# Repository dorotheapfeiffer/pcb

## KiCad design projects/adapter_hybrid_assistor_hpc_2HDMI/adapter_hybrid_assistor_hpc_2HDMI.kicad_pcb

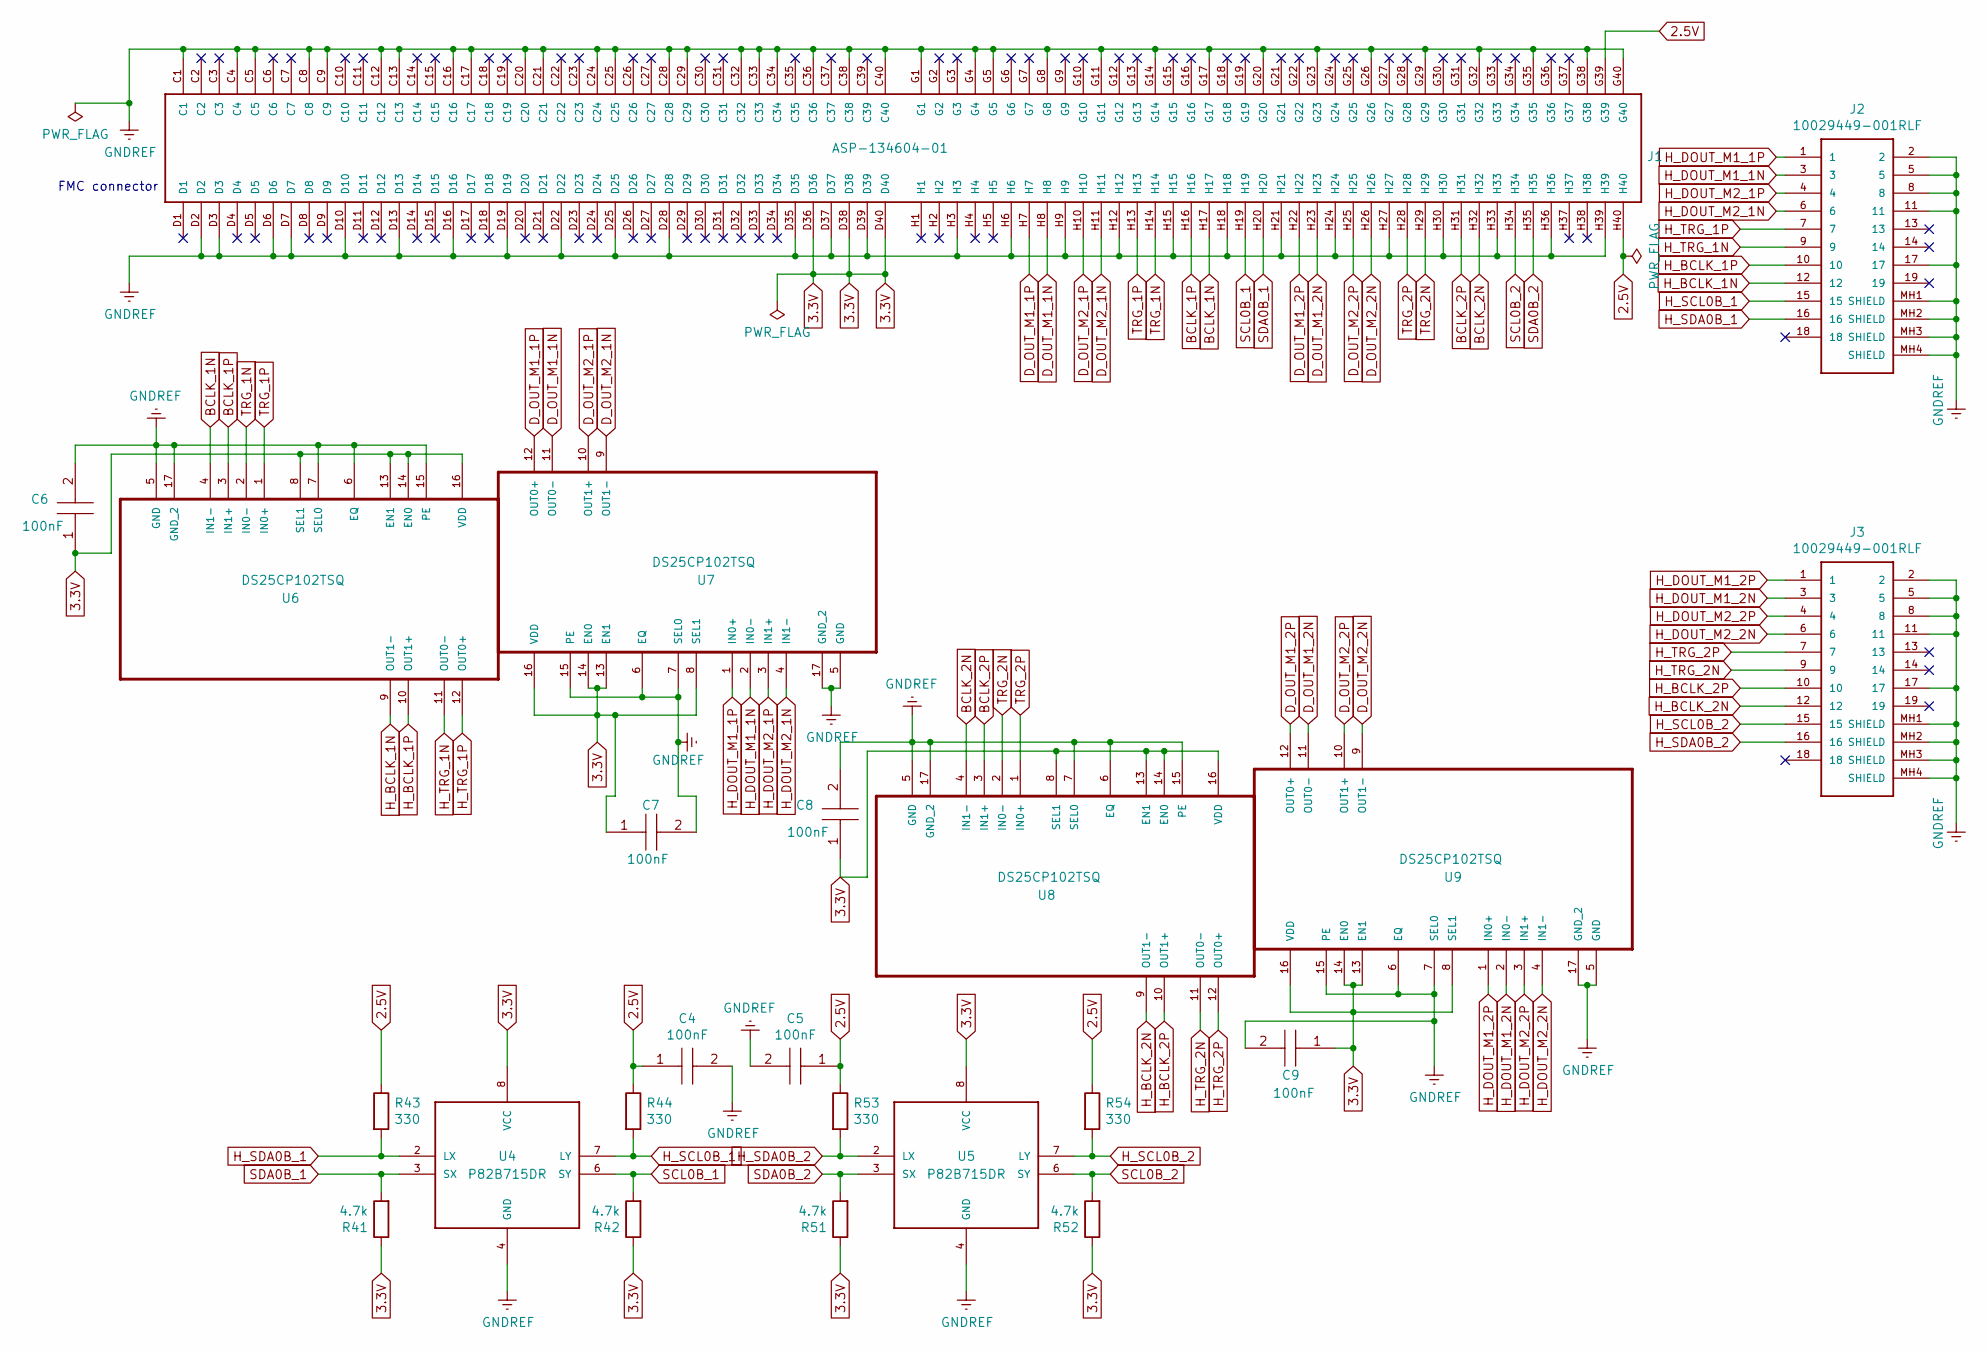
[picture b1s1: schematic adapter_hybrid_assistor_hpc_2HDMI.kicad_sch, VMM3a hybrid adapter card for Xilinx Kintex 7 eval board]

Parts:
C4, C5, C6, C7, C8, C9: 100nF; C0603C104K4RACTU; Manufacturer_Part_Number C0603C104K4RACTU; Mouser Part Number 80-C0603C104K4R
J1: ASP-134604-01; Samtec_FMC_ASP-134604-01_4x40_Vertical
J2, J3: 10029449-001RLF; 10029449001RLF
R41, R42, R51, R52: 4.7k; R_0603_1608Metric
R43, R44, R53, R54: 330; R_0603_1608Metric
U4, U5: P82B715DR
U6, U7, U8, U9: DS25CP102TSQ; QFN50P400X400X80-17N

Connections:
2.5V: C4.1, C5.1, J1.G39, J1.H40, R43.1, R44.1, R53.1, R54.1
3.3V: C6.1, C7.1, C8.1, C9.1, J1.D36, J1.D38, J1.D40, R41.1, R42.1, R51.1, R52.1, U4.8 (VCC), U5.8 (VCC), U6.8 (SEL1), U6.13 (EN1), U6.14 (EN0), U6.16 (VDD), U7.8 (SEL1), U7.13 (EN1), U7.14 (EN0), U7.16 (VDD), U8.8 (SEL1), U8.13 (EN1), U8.14 (EN0), U8.16 (VDD), U9.8 (SEL1), U9.13 (EN1), U9.14 (EN0), U9.16 (VDD)
BCLK_1N: J1.H17, U6.4 (IN1-)
BCLK_1P: J1.H16, U6.3 (IN1+)
BCLK_2N: J1.H32, U8.4 (IN1-)
BCLK_2P: J1.H31, U8.3 (IN1+)
D_OUT_M1_1N: J1.H8, U7.11 (OUT0-)
D_OUT_M1_1P: J1.H7, U7.12 (OUT0+)
D_OUT_M1_2N: J1.H23, U9.11 (OUT0-)
D_OUT_M1_2P: J1.H22, U9.12 (OUT0+)
D_OUT_M2_1N: J1.H11, U7.9 (OUT1-)
D_OUT_M2_1P: J1.H10, U7.10 (OUT1+)
D_OUT_M2_2N: J1.H26, U9.9 (OUT1-)
D_OUT_M2_2P: J1.H25, U9.10 (OUT1+)
GNDREF: C4.2, C5.2, C6.2, C7.2, C8.2, C9.2, J1.C1, J1.C4, J1.C5, J1.C8, J1.C9, J1.C12, J1.C13, J1.C16, J1.C17, J1.C20, J1.C21, J1.C24, J1.C25, J1.C28, J1.C29, J1.C32, J1.C33, J1.C34, J1.C36, J1.C38, J1.C40, J1.D2, J1.D3, J1.D6, J1.D7, J1.D10, J1.D13, J1.D16, J1.D19, J1.D22, J1.D25, J1.D28, J1.D35, J1.D37, J1.D39, J1.G1, J1.G4, J1.G5, J1.G8, J1.G11, J1.G14, J1.G17, J1.G20, J1.G23, J1.G26, J1.G29, J1.G32, J1.G35, J1.G38, J1.G40, J1.H3, J1.H6, J1.H9, J1.H12, J1.H15, J1.H18, J1.H21, J1.H24, J1.H27, J1.H30, J1.H33, J1.H36, J1.H39, J2.2, J2.5, J2.8, J2.11, J2.17, J2.MH1 (SHIELD), J2.MH2 (SHIELD), J2.MH3 (SHIELD), J2.MH4 (SHIELD), J3.2, J3.5, J3.8, J3.11, J3.17, J3.MH1 (SHIELD), J3.MH2 (SHIELD), J3.MH3 (SHIELD), J3.MH4 (SHIELD), U4.4 (GND), U5.4 (GND), U6.5 (GND), U6.6 (EQ), U6.7 (SEL0), U6.15 (PE), U6.17 (GND_2), U7.5 (GND), U7.6 (EQ), U7.7 (SEL0), U7.15 (PE), U7.17 (GND_2), U8.5 (GND), U8.6 (EQ), U8.7 (SEL0), U8.15 (PE), U8.17 (GND_2), U9.5 (GND), U9.6 (EQ), U9.7 (SEL0), U9.15 (PE), U9.17 (GND_2)
H_BCLK_1N: J2.12, U6.9 (OUT1-)
H_BCLK_1P: J2.10, U6.10 (OUT1+)
H_BCLK_2N: J3.12, U8.9 (OUT1-)
H_BCLK_2P: J3.10, U8.10 (OUT1+)
H_DOUT_M1_1N: J2.3, U7.2 (IN0-)
H_DOUT_M1_1P: J2.1, U7.1 (IN0+)
H_DOUT_M1_2N: J3.3, U9.2 (IN0-)
H_DOUT_M1_2P: J3.1, U9.1 (IN0+)
H_DOUT_M2_1N: J2.6, U7.4 (IN1-)
H_DOUT_M2_1P: J2.4, U7.3 (IN1+)
H_DOUT_M2_2N: J3.6, U9.4 (IN1-)
H_DOUT_M2_2P: J3.4, U9.3 (IN1+)
H_SCL0B_1: J2.15, R44.2, U4.7 (LY)
H_SCL0B_2: J3.15, R54.2, U5.7 (LY)
H_SDA0B_1: J2.16, R43.2, U4.2 (LX)
H_SDA0B_2: J3.16, R53.2, U5.2 (LX)
H_TRG_1N: J2.9, U6.11 (OUT0-)
H_TRG_1P: J2.7, U6.12 (OUT0+)
H_TRG_2N: J3.9, U8.11 (OUT0-)
H_TRG_2P: J3.7, U8.12 (OUT0+)
SCL0B_1: J1.H19, R42.2, U4.6 (SY)
SCL0B_2: J1.H34, R52.2, U5.6 (SY)
SDA0B_1: J1.H20, R41.2, U4.3 (SX)
SDA0B_2: J1.H35, R51.2, U5.3 (SX)
TRG_1N: J1.H14, U6.2 (IN0-)
TRG_1P: J1.H13, U6.1 (IN0+)
TRG_2N: J1.H29, U8.2 (IN0-)
TRG_2P: J1.H28, U8.1 (IN0+)

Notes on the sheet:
FMC connector

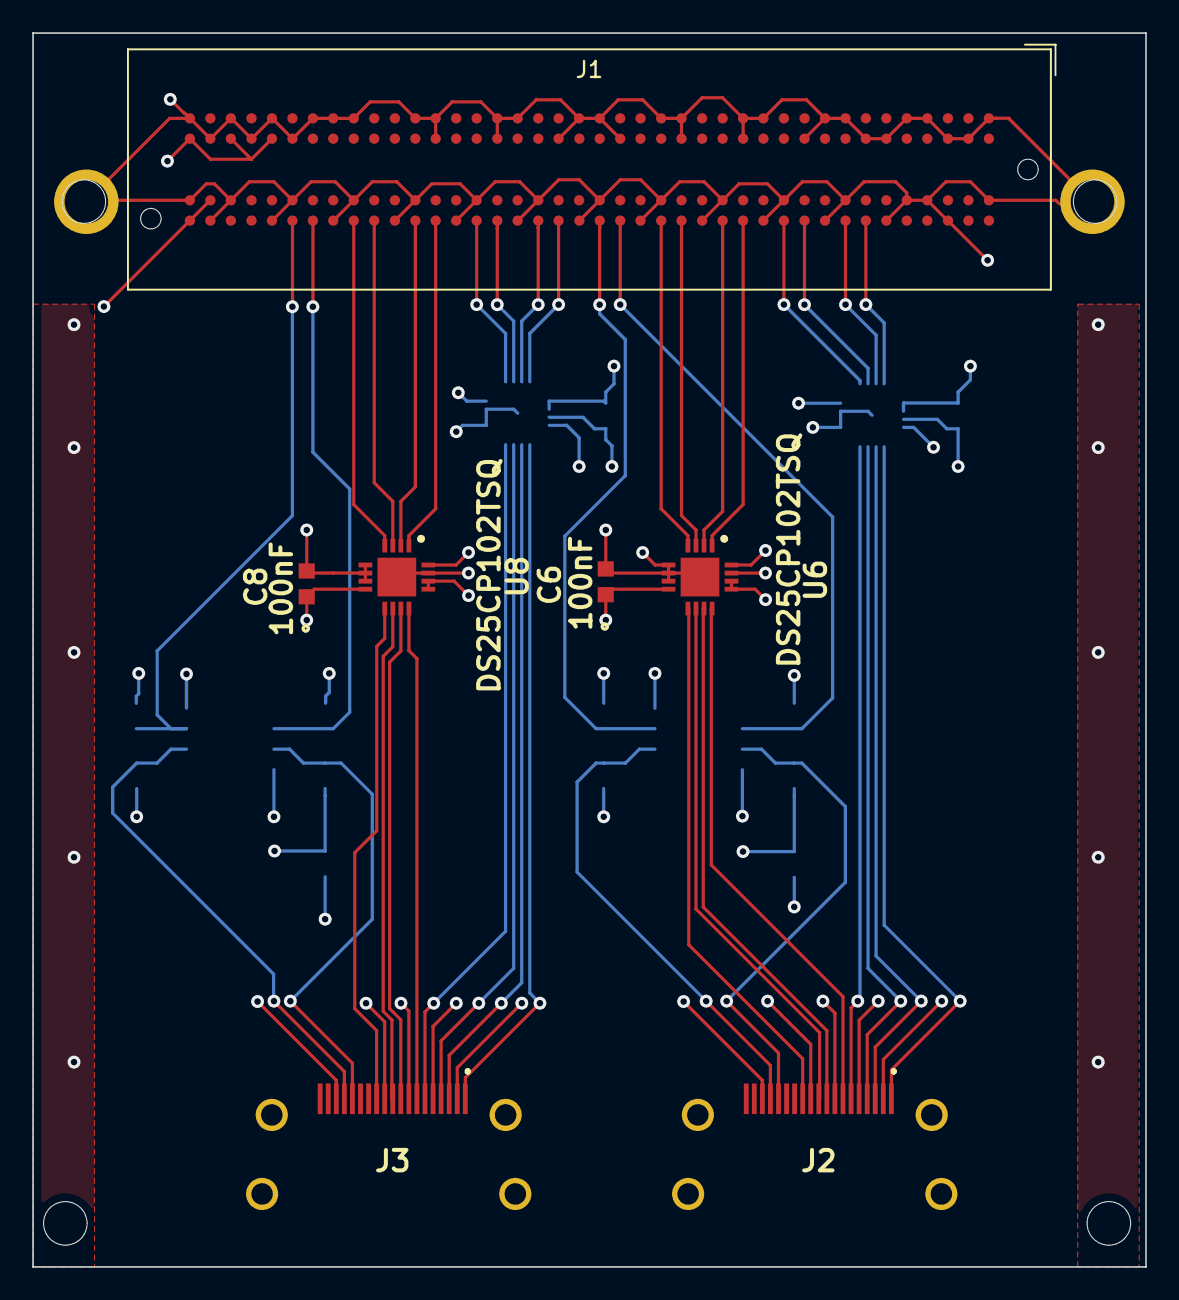
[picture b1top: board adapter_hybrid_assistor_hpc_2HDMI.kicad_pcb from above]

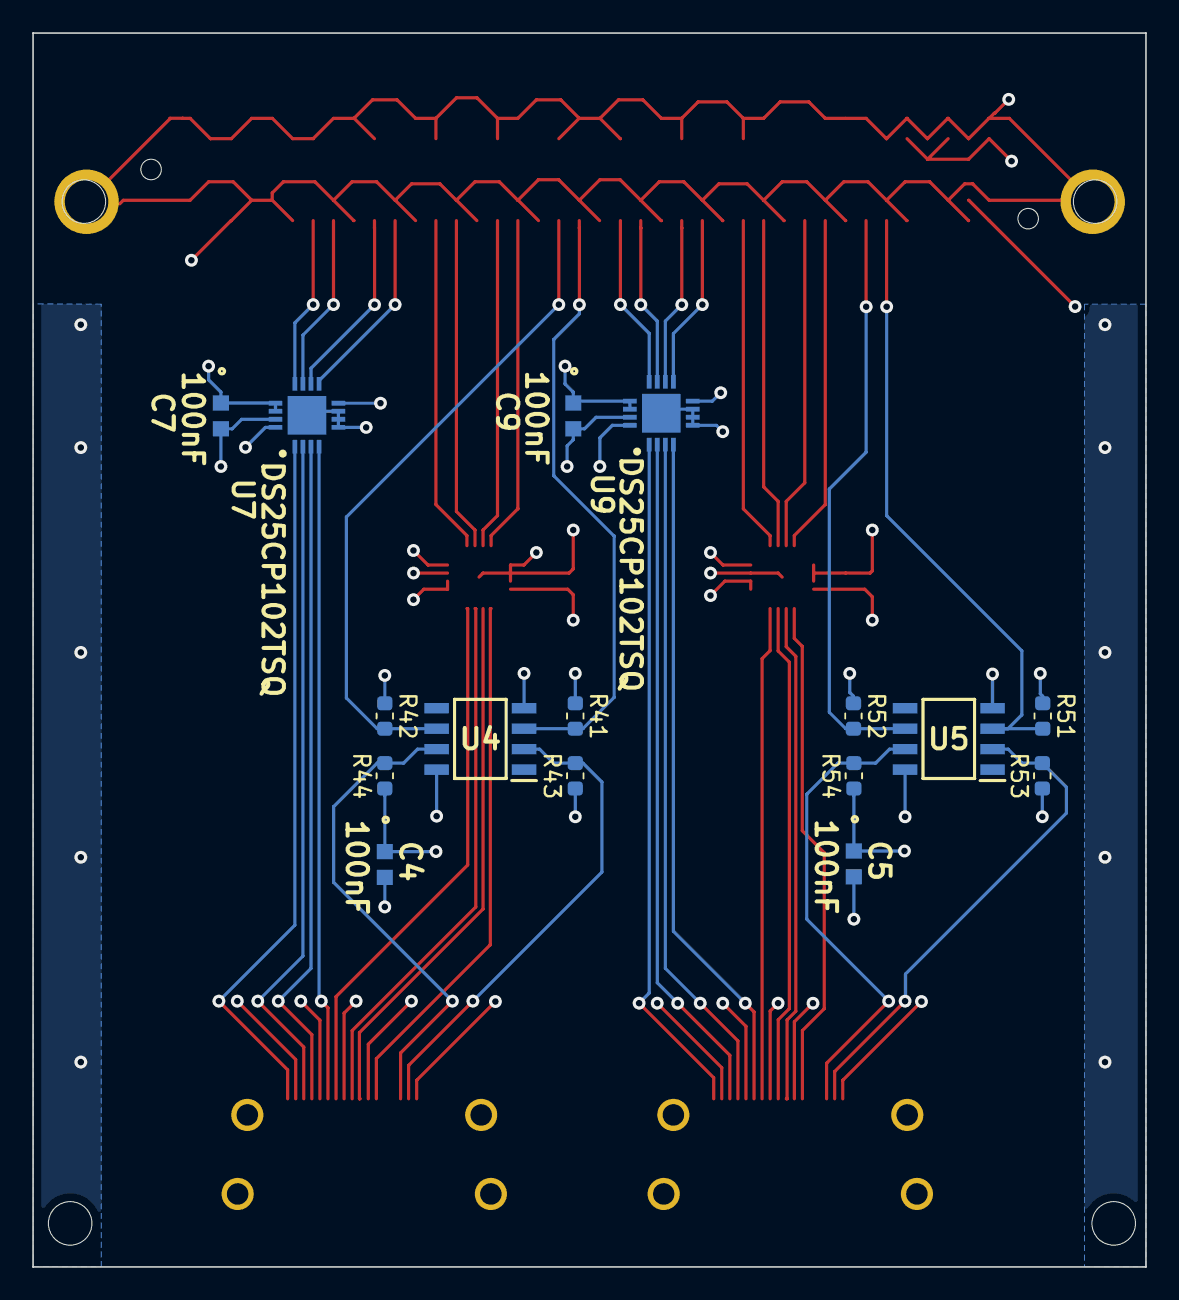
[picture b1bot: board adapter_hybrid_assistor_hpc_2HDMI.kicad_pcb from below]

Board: 4 copper layers, 69.0 x 76.5 mm, 23 parts (16 on the bottom side), 43 nets.

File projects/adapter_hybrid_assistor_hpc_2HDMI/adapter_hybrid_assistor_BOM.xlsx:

Id | Designator | Designation | Package | Quantity | Value | Place_YES/NO | Provided_by_customer_YES/NO | Supplier | Supplier ref | Manufacturer | Montage
2 | J1 | ASP13460401 |  | 1 |  | YES | NO | Mouser | 200-ASP-134604-01 | Samtec | Solder Balls
6 | U7,U6,U9,U8 | DS25CP102TSQ | WQFN-16 | 4 |  | YES | NO | Mouser | 926-DS25CP102TSQNOPB | Texas Instruments | SMD/SMT
7 | U5,U4 | P82B715DR | SOIC-8 | 2 |  | YES | NO | Mouser | 595-P82B715DR | Texas Instruments | SMD/SMT
11 | J2,J3 | 10029449001RLF |  | 2 |  | YES | NO | Mouser | 649-10029449-001RLF | Amphenol FCI | SMD/SMT
12 | R41,R42,R51,R52 | ERA-3ARB472V | 0603 (1608 metric) | 4 | 4.7k | YES | NO | Mouser | ERA3ARB472V | Panasonic | SMD/SMT | ERA3ARB472V
14 | R43,R44,R53,R54 | ERA-3AED331V | 0603 (1608 metric) | 4 | 330 | YES | NO | Mouser | ERA3AEB331V | Panasonic | SMD/SMT | ERA3AEB331V
15 | C4,C5,C6,C7,C8,C9 | C0603C104K4RACTU | 0603 (1608 metric) | 6 | 100nF | YES | NO | Mouser | 80-C0603C104K4R | KEMET | SMD/SMT
 |  |  |  | 23

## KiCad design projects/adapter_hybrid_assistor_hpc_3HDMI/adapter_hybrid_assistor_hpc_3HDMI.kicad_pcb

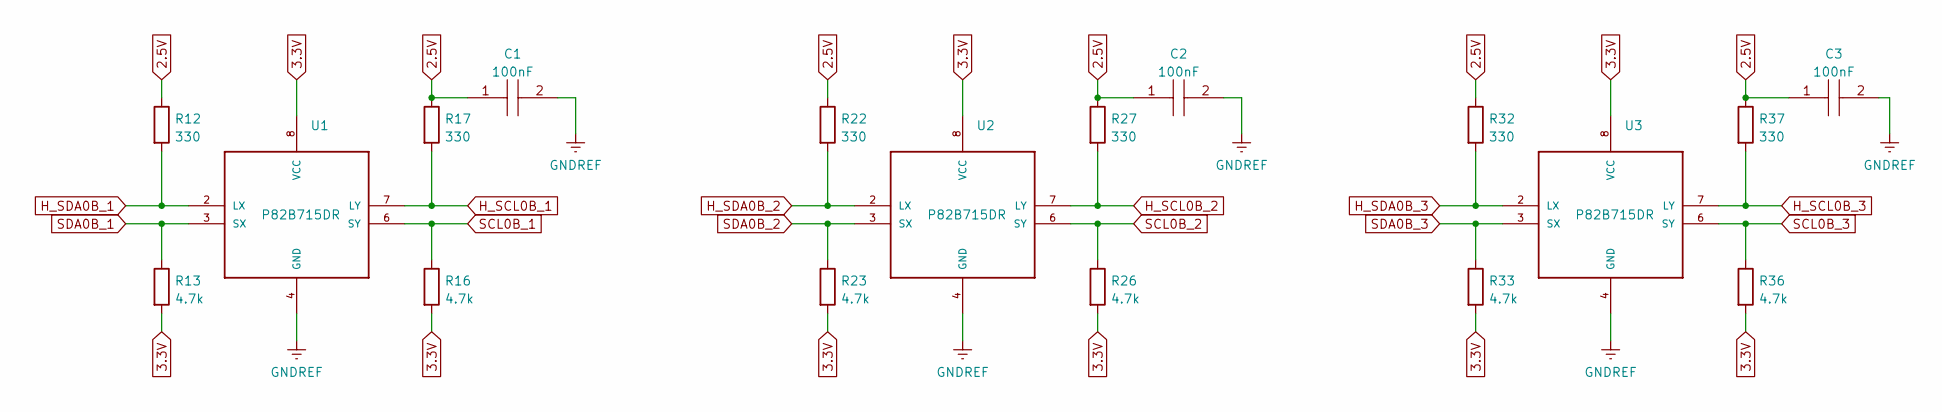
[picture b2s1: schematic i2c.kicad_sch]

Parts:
C1, C2, C3: 100nF; C0603C104K4RACTU; Manufacturer_Part_Number C0603C104K4RACTU; Mouser Part Number 80-C0603C104K4R
R12, R17, R22, R27, R32, R37: 330; R_0603_1608Metric
R13, R16, R23, R26, R33, R36: 4.7k; R_0603_1608Metric
U1, U2, U3: P82B715DR

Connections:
2.5V: C1.1, C2.1, C3.1, R12.1, R17.1, R22.1, R27.1, R32.1, R37.1; also elsewhere on the board
3.3V: R13.2, R16.2, R23.2, R26.2, R33.2, R36.2, U1.8 (VCC), U2.8 (VCC), U3.8 (VCC); also elsewhere on the board
H_SCL0B_1: R17.2, U1.7 (LY); also elsewhere on the board
H_SCL0B_2: R27.2, U2.7 (LY); also elsewhere on the board
H_SCL0B_3: R37.2, U3.7 (LY); also elsewhere on the board
H_SDA0B_1: R12.2, U1.2 (LX); also elsewhere on the board
H_SDA0B_2: R22.2, U2.2 (LX); also elsewhere on the board
H_SDA0B_3: R32.2, U3.2 (LX); also elsewhere on the board
SCL0B_1: R16.1, U1.6 (SY); also elsewhere on the board
SCL0B_2: R26.1, U2.6 (SY); also elsewhere on the board
SCL0B_3: R36.1, U3.6 (SY); also elsewhere on the board
SDA0B_1: R13.1, U1.3 (SX); also elsewhere on the board
SDA0B_2: R23.1, U2.3 (SX); also elsewhere on the board
SDA0B_3: R33.1, U3.3 (SX); also elsewhere on the board

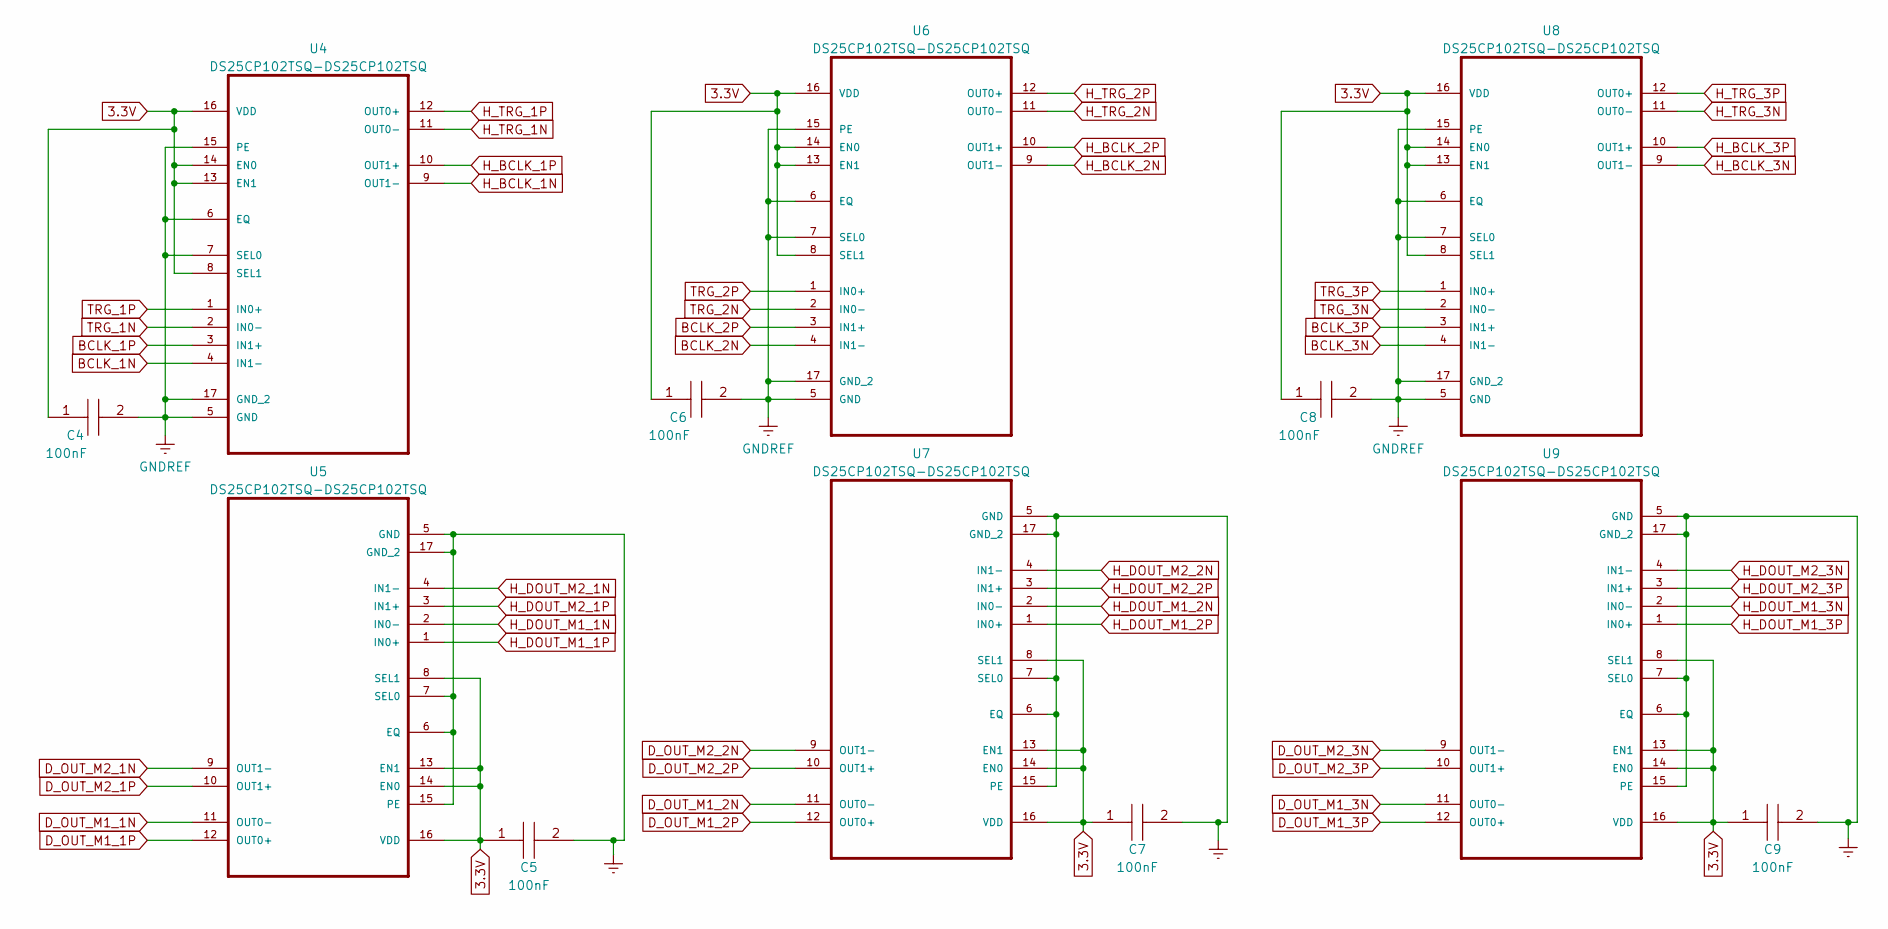
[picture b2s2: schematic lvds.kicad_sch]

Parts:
C4, C5, C6, C7, C8, C9: 100nF; C0603C104K4RACTU; Manufacturer_Part_Number C0603C104K4RACTU; Mouser Part Number 80-C0603C104K4R
U4, U5, U6, U7, U8, U9: DS25CP102TSQ-DS25CP102TSQ; QFN50P400X400X80-17N

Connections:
3.3V: C4.1, C5.1, C6.1, C7.1, C8.1, C9.1, U4.8 (SEL1), U4.13 (EN1), U4.14 (EN0), U4.16 (VDD), U5.8 (SEL1), U5.13 (EN1), U5.14 (EN0), U5.16 (VDD), U6.8 (SEL1), U6.13 (EN1), U6.14 (EN0), U6.16 (VDD), U7.8 (SEL1), U7.13 (EN1), U7.14 (EN0), U7.16 (VDD), U8.8 (SEL1), U8.13 (EN1), U8.14 (EN0), U8.16 (VDD), U9.8 (SEL1), U9.13 (EN1), U9.14 (EN0), U9.16 (VDD); also elsewhere on the board
BCLK_1N: U4.4 (IN1-); also elsewhere on the board
BCLK_1P: U4.3 (IN1+); also elsewhere on the board
BCLK_2N: U6.4 (IN1-); also elsewhere on the board
BCLK_2P: U6.3 (IN1+); also elsewhere on the board
BCLK_3N: U8.4 (IN1-); also elsewhere on the board
BCLK_3P: U8.3 (IN1+); also elsewhere on the board
D_OUT_M1_1N: U5.11 (OUT0-); also elsewhere on the board
D_OUT_M1_1P: U5.12 (OUT0+); also elsewhere on the board
D_OUT_M1_2N: U7.11 (OUT0-); also elsewhere on the board
D_OUT_M1_2P: U7.12 (OUT0+); also elsewhere on the board
D_OUT_M1_3N: U9.11 (OUT0-); also elsewhere on the board
D_OUT_M1_3P: U9.12 (OUT0+); also elsewhere on the board
D_OUT_M2_1N: U5.9 (OUT1-); also elsewhere on the board
D_OUT_M2_1P: U5.10 (OUT1+); also elsewhere on the board
D_OUT_M2_2N: U7.9 (OUT1-); also elsewhere on the board
D_OUT_M2_2P: U7.10 (OUT1+); also elsewhere on the board
D_OUT_M2_3N: U9.9 (OUT1-); also elsewhere on the board
D_OUT_M2_3P: U9.10 (OUT1+); also elsewhere on the board
H_BCLK_1N: U4.9 (OUT1-); also elsewhere on the board
H_BCLK_1P: U4.10 (OUT1+); also elsewhere on the board
H_BCLK_2N: U6.9 (OUT1-); also elsewhere on the board
H_BCLK_2P: U6.10 (OUT1+); also elsewhere on the board
H_BCLK_3N: U8.9 (OUT1-); also elsewhere on the board
H_BCLK_3P: U8.10 (OUT1+); also elsewhere on the board
H_DOUT_M1_1N: U5.2 (IN0-); also elsewhere on the board
H_DOUT_M1_1P: U5.1 (IN0+); also elsewhere on the board
H_DOUT_M1_2N: U7.2 (IN0-); also elsewhere on the board
H_DOUT_M1_2P: U7.1 (IN0+); also elsewhere on the board
H_DOUT_M1_3N: U9.2 (IN0-); also elsewhere on the board
H_DOUT_M1_3P: U9.1 (IN0+); also elsewhere on the board
H_DOUT_M2_1N: U5.4 (IN1-); also elsewhere on the board
H_DOUT_M2_1P: U5.3 (IN1+); also elsewhere on the board
H_DOUT_M2_2N: U7.4 (IN1-); also elsewhere on the board
H_DOUT_M2_2P: U7.3 (IN1+); also elsewhere on the board
H_DOUT_M2_3N: U9.4 (IN1-); also elsewhere on the board
H_DOUT_M2_3P: U9.3 (IN1+); also elsewhere on the board
H_TRG_1N: U4.11 (OUT0-); also elsewhere on the board
H_TRG_1P: U4.12 (OUT0+); also elsewhere on the board
H_TRG_2N: U6.11 (OUT0-); also elsewhere on the board
H_TRG_2P: U6.12 (OUT0+); also elsewhere on the board
H_TRG_3N: U8.11 (OUT0-); also elsewhere on the board
H_TRG_3P: U8.12 (OUT0+); also elsewhere on the board
TRG_1N: U4.2 (IN0-); also elsewhere on the board
TRG_1P: U4.1 (IN0+); also elsewhere on the board
TRG_2N: U6.2 (IN0-); also elsewhere on the board
TRG_2P: U6.1 (IN0+); also elsewhere on the board
TRG_3N: U8.2 (IN0-); also elsewhere on the board
TRG_3P: U8.1 (IN0+); also elsewhere on the board

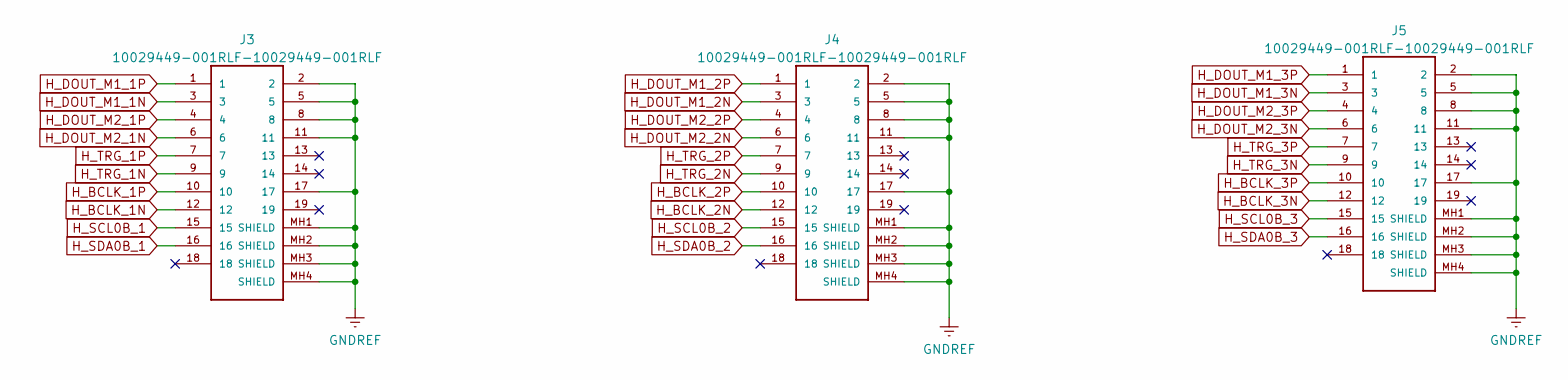
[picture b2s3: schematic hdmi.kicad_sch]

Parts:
J3, J4, J5: 10029449-001RLF-10029449-001RLF; 10029449001RLF

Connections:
H_BCLK_1N: J3.12; also elsewhere on the board
H_BCLK_1P: J3.10; also elsewhere on the board
H_BCLK_2N: J4.12; also elsewhere on the board
H_BCLK_2P: J4.10; also elsewhere on the board
H_BCLK_3N: J5.12; also elsewhere on the board
H_BCLK_3P: J5.10; also elsewhere on the board
H_DOUT_M1_1N: J3.3; also elsewhere on the board
H_DOUT_M1_1P: J3.1; also elsewhere on the board
H_DOUT_M1_2N: J4.3; also elsewhere on the board
H_DOUT_M1_2P: J4.1; also elsewhere on the board
H_DOUT_M1_3N: J5.3; also elsewhere on the board
H_DOUT_M1_3P: J5.1; also elsewhere on the board
H_DOUT_M2_1N: J3.6; also elsewhere on the board
H_DOUT_M2_1P: J3.4; also elsewhere on the board
H_DOUT_M2_2N: J4.6; also elsewhere on the board
H_DOUT_M2_2P: J4.4; also elsewhere on the board
H_DOUT_M2_3N: J5.6; also elsewhere on the board
H_DOUT_M2_3P: J5.4; also elsewhere on the board
H_SCL0B_1: J3.15; also elsewhere on the board
H_SCL0B_2: J4.15; also elsewhere on the board
H_SCL0B_3: J5.15; also elsewhere on the board
H_SDA0B_1: J3.16; also elsewhere on the board
H_SDA0B_2: J4.16; also elsewhere on the board
H_SDA0B_3: J5.16; also elsewhere on the board
H_TRG_1N: J3.9; also elsewhere on the board
H_TRG_1P: J3.7; also elsewhere on the board
H_TRG_2N: J4.9; also elsewhere on the board
H_TRG_2P: J4.7; also elsewhere on the board
H_TRG_3N: J5.9; also elsewhere on the board
H_TRG_3P: J5.7; also elsewhere on the board

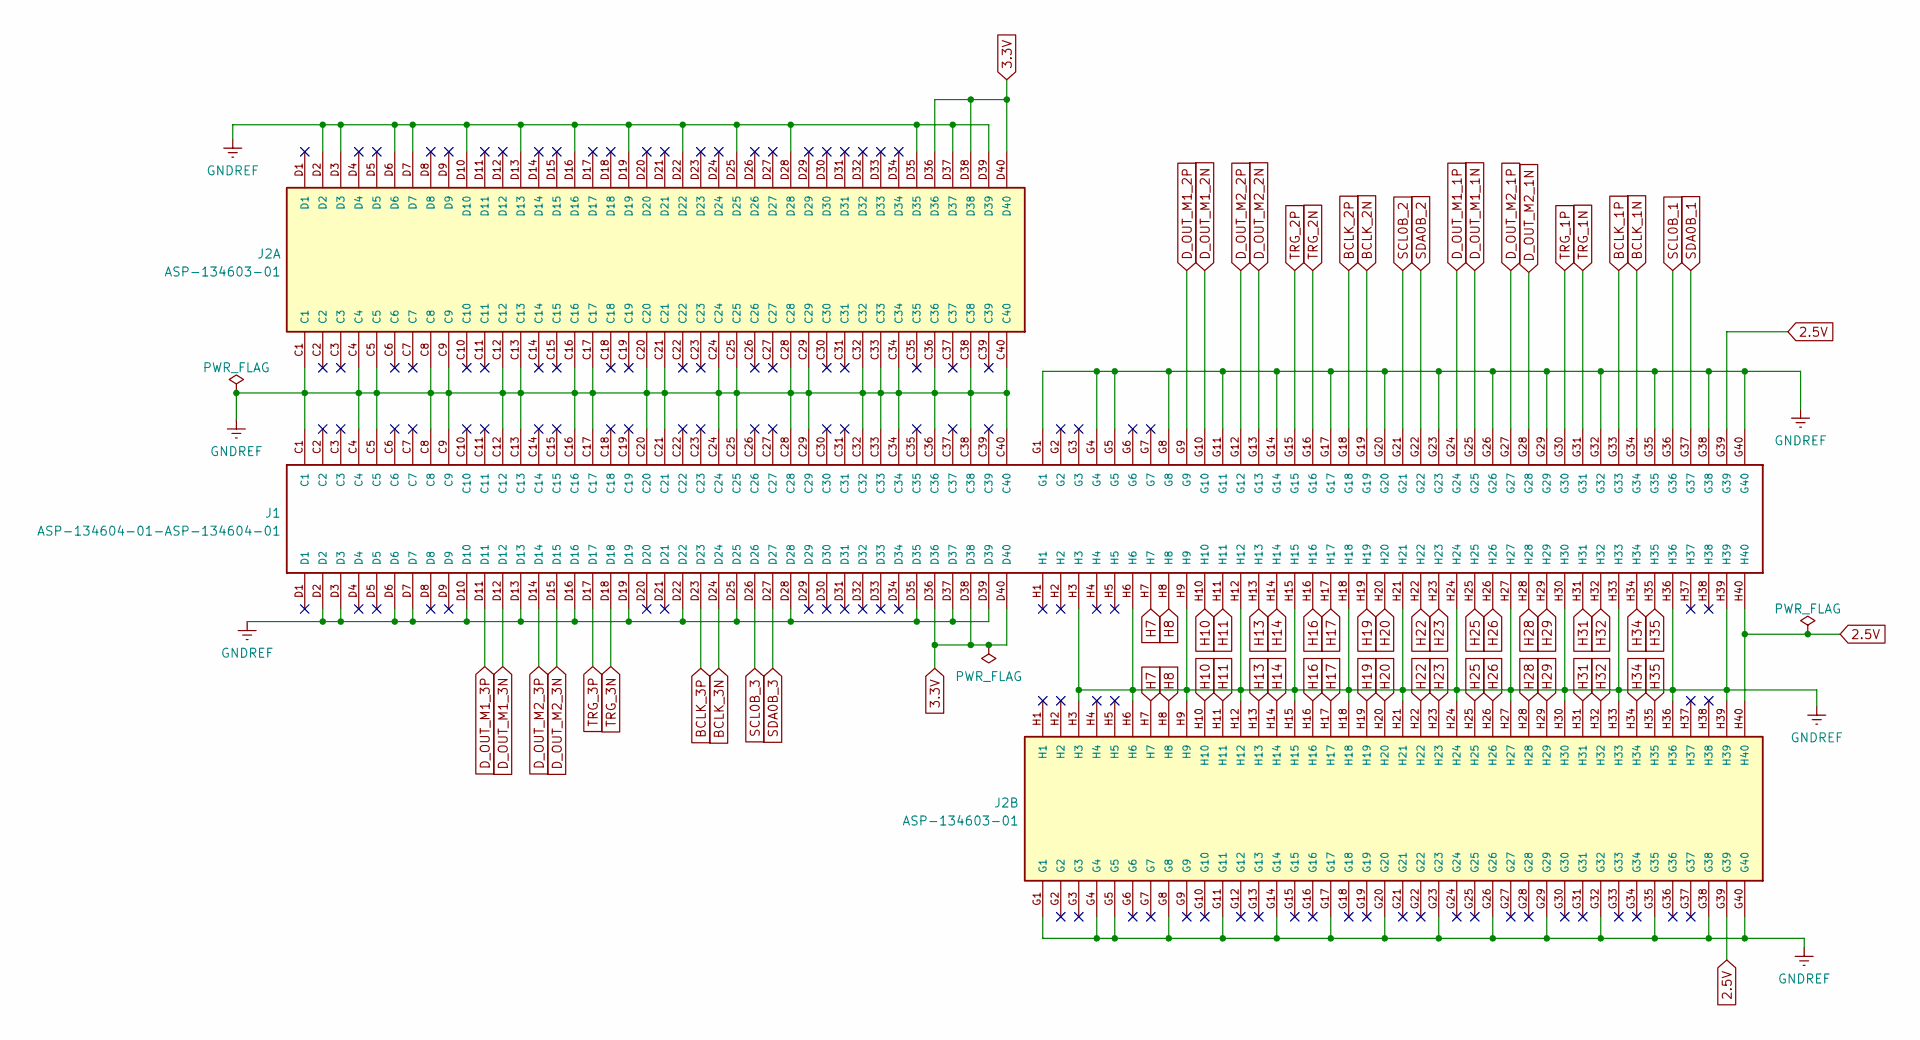
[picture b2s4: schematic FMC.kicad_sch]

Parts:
J1: ASP-134604-01-ASP-134604-01; Samtec_FMC_ASP-134604-01_4x40_Vertical
J2: ASP-134603-01; SAMTEC_ASP-134603-01; PARTREV M

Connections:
2.5V: J1.G39, J1.H40, J2.G39, J2.H40; also elsewhere on the board
3.3V: J1.D36, J1.D38, J1.D40, J2.D36, J2.D38, J2.D40; also elsewhere on the board
BCLK_1N: J1.G34; also elsewhere on the board
BCLK_1P: J1.G33; also elsewhere on the board
BCLK_2N: J1.G19; also elsewhere on the board
BCLK_2P: J1.G18; also elsewhere on the board
BCLK_3N: J1.D24; also elsewhere on the board
BCLK_3P: J1.D23; also elsewhere on the board
D_OUT_M1_1N: J1.G25; also elsewhere on the board
D_OUT_M1_1P: J1.G24; also elsewhere on the board
D_OUT_M1_2N: J1.G10; also elsewhere on the board
D_OUT_M1_2P: J1.G9; also elsewhere on the board
D_OUT_M1_3N: J1.D12; also elsewhere on the board
D_OUT_M1_3P: J1.D11; also elsewhere on the board
D_OUT_M2_1N: J1.G28; also elsewhere on the board
D_OUT_M2_1P: J1.G27; also elsewhere on the board
D_OUT_M2_2N: J1.G13; also elsewhere on the board
D_OUT_M2_2P: J1.G12; also elsewhere on the board
D_OUT_M2_3N: J1.D15; also elsewhere on the board
D_OUT_M2_3P: J1.D14; also elsewhere on the board
H7: J1.H7, J2.H7
H8: J1.H8, J2.H8
H10: J1.H10, J2.H10
H11: J1.H11, J2.H11
H13: J1.H13, J2.H13
H14: J1.H14, J2.H14
H16: J1.H16, J2.H16
H17: J1.H17, J2.H17
H19: J1.H19, J2.H19
H20: J1.H20, J2.H20
H22: J1.H22, J2.H22
H23: J1.H23, J2.H23
H25: J1.H25, J2.H25
H26: J1.H26, J2.H26
H28: J1.H28, J2.H28
H29: J1.H29, J2.H29
H31: J1.H31, J2.H31
H32: J1.H32, J2.H32
H34: J1.H34, J2.H34
H35: J1.H35, J2.H35
SCL0B_1: J1.G36; also elsewhere on the board
SCL0B_2: J1.G21; also elsewhere on the board
SCL0B_3: J1.D26; also elsewhere on the board
SDA0B_1: J1.G37; also elsewhere on the board
SDA0B_2: J1.G22; also elsewhere on the board
SDA0B_3: J1.D27; also elsewhere on the board
TRG_1N: J1.G31; also elsewhere on the board
TRG_1P: J1.G30; also elsewhere on the board
TRG_2N: J1.G16; also elsewhere on the board
TRG_2P: J1.G15; also elsewhere on the board
TRG_3N: J1.D18; also elsewhere on the board
TRG_3P: J1.D17; also elsewhere on the board

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
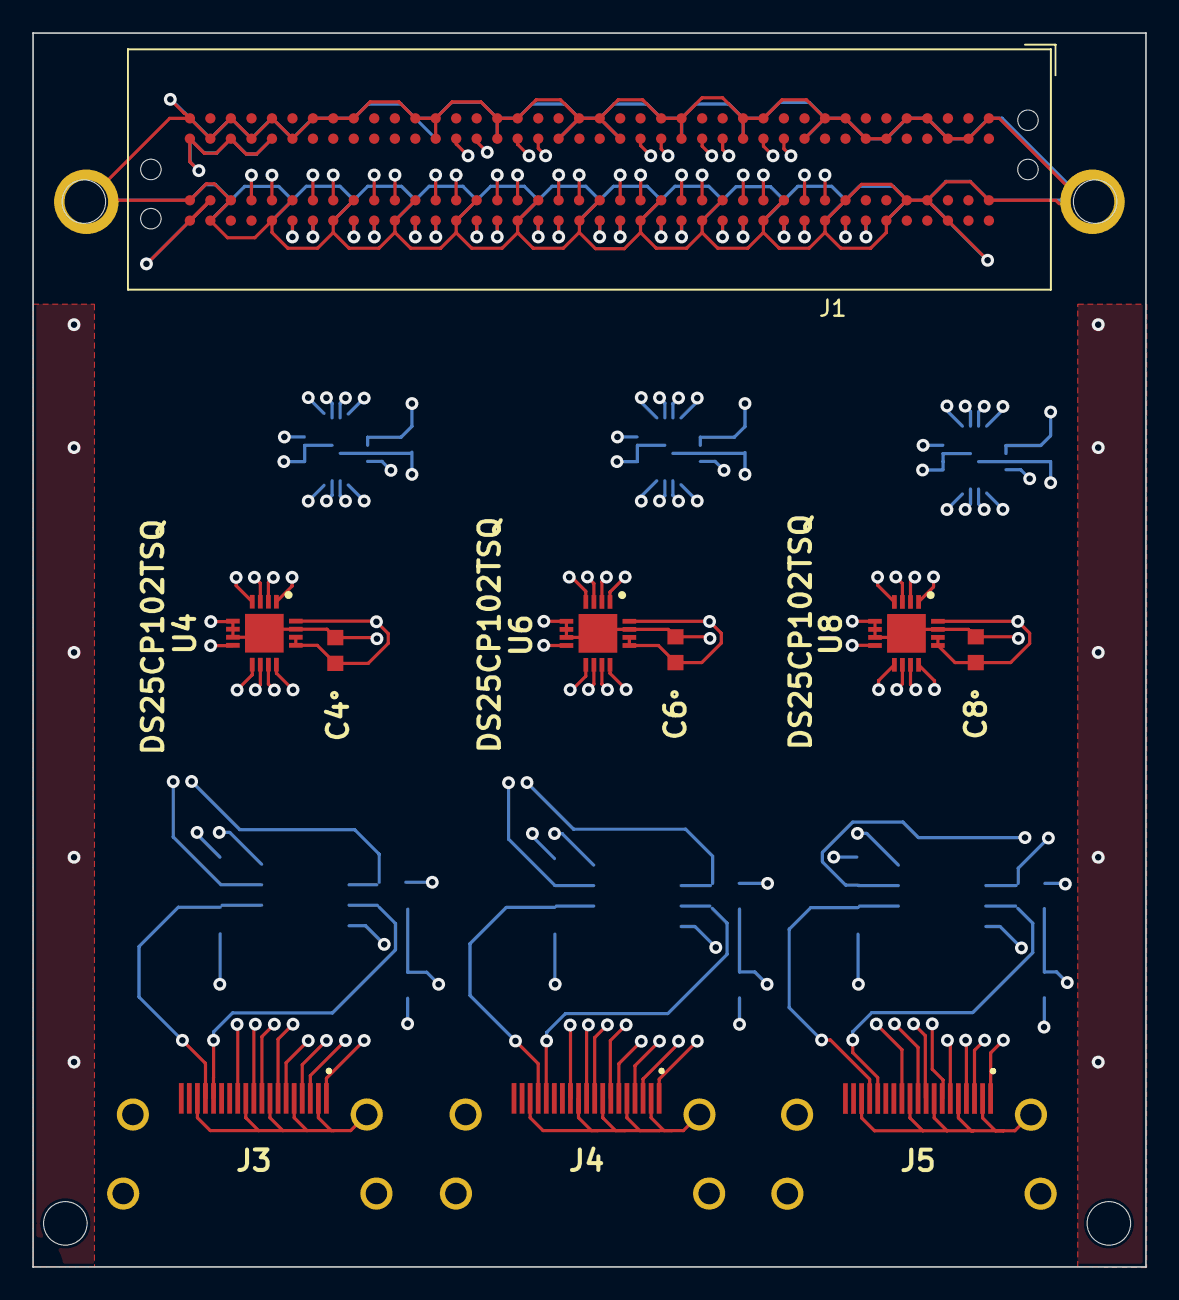
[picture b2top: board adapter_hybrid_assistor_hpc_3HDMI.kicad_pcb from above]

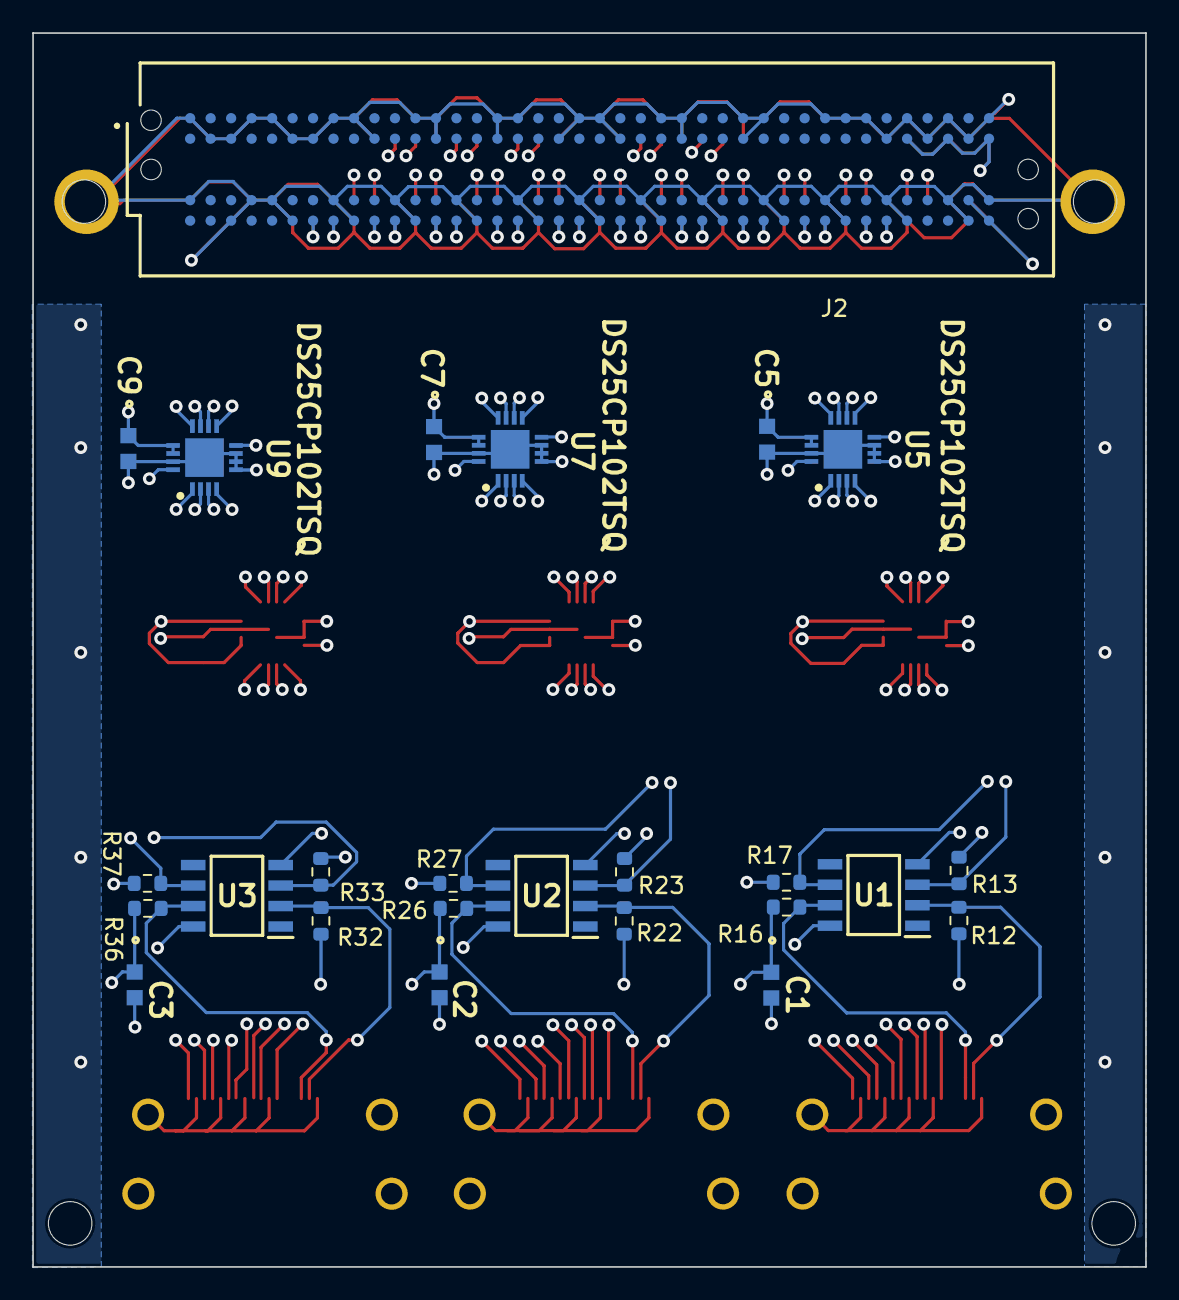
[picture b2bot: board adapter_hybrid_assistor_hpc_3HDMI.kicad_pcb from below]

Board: 6 copper layers, 69.0 x 76.5 mm, 35 parts (25 on the bottom side), 83 nets.

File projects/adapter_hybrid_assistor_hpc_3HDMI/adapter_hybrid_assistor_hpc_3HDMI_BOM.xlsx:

Id | Designator | Designation | Package | Quantity | Value | Place_YES/NO | Provided_by_customer_YES/NO | Supplier | Supplier ref | Manufacturer | Montage
2 | J1 | ASP13460401 |  | 1 |  | YES | NO | Mouser | 200-ASP-134604-01 | Samtec | Solder Balls | 4
 | J2 | ASP-134603 |  |  |  |  |  |  | ASP-134603-01 |  |  | 2
 | J3, J5, J4 | 10029449001RLF |  | 2 |  | YES | NO | Mouser | 649-10029449-001RLF | Amphenol FCI | SMD/SMT | 15
 | R12, R27, R22, R32 | ERA-3AED331V | 0603 (1608 metric) | 4 | 330 | YES | NO | Mouser | 667-ERA-3AED331V | Panasonic | SMD/SMT
 | R26, R36, R16, R23 | ERA-3ARB472V | 0603 (1608 metric) | 4 | 4.7k | YES | NO | Mouser | 667-ERA-3ARB472V | Panasonic | SMD/SMT
 | U1, U3, U2 | P82B715DR | SOIC-8 | 2 |  | YES | NO | Mouser | 595-P82B715DR | Texas Instruments | SMD/SMT
 | U4, U8, U6, U7, U9, U5 | DS25CP102TSQ | WQFN-16 | 4 |  | YES | NO | Mouser | 926-DS25CP102TSQNOPB | Texas Instruments | SMD/SMT | 18
 | C4, C8, C6, C5, C7, C9 | C0603C104K4RACTU | 0603 (1608 metric) | 6 | 100nF | YES | NO | Mouser | 80-C0603C104K4R | KEMET | SMD/SMT | 100
